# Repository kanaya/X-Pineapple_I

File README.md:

# Pineapple I

Pineapple I is a MIDI-connected 12-way LED driver. Please read doc/pineapple1.md for more info.

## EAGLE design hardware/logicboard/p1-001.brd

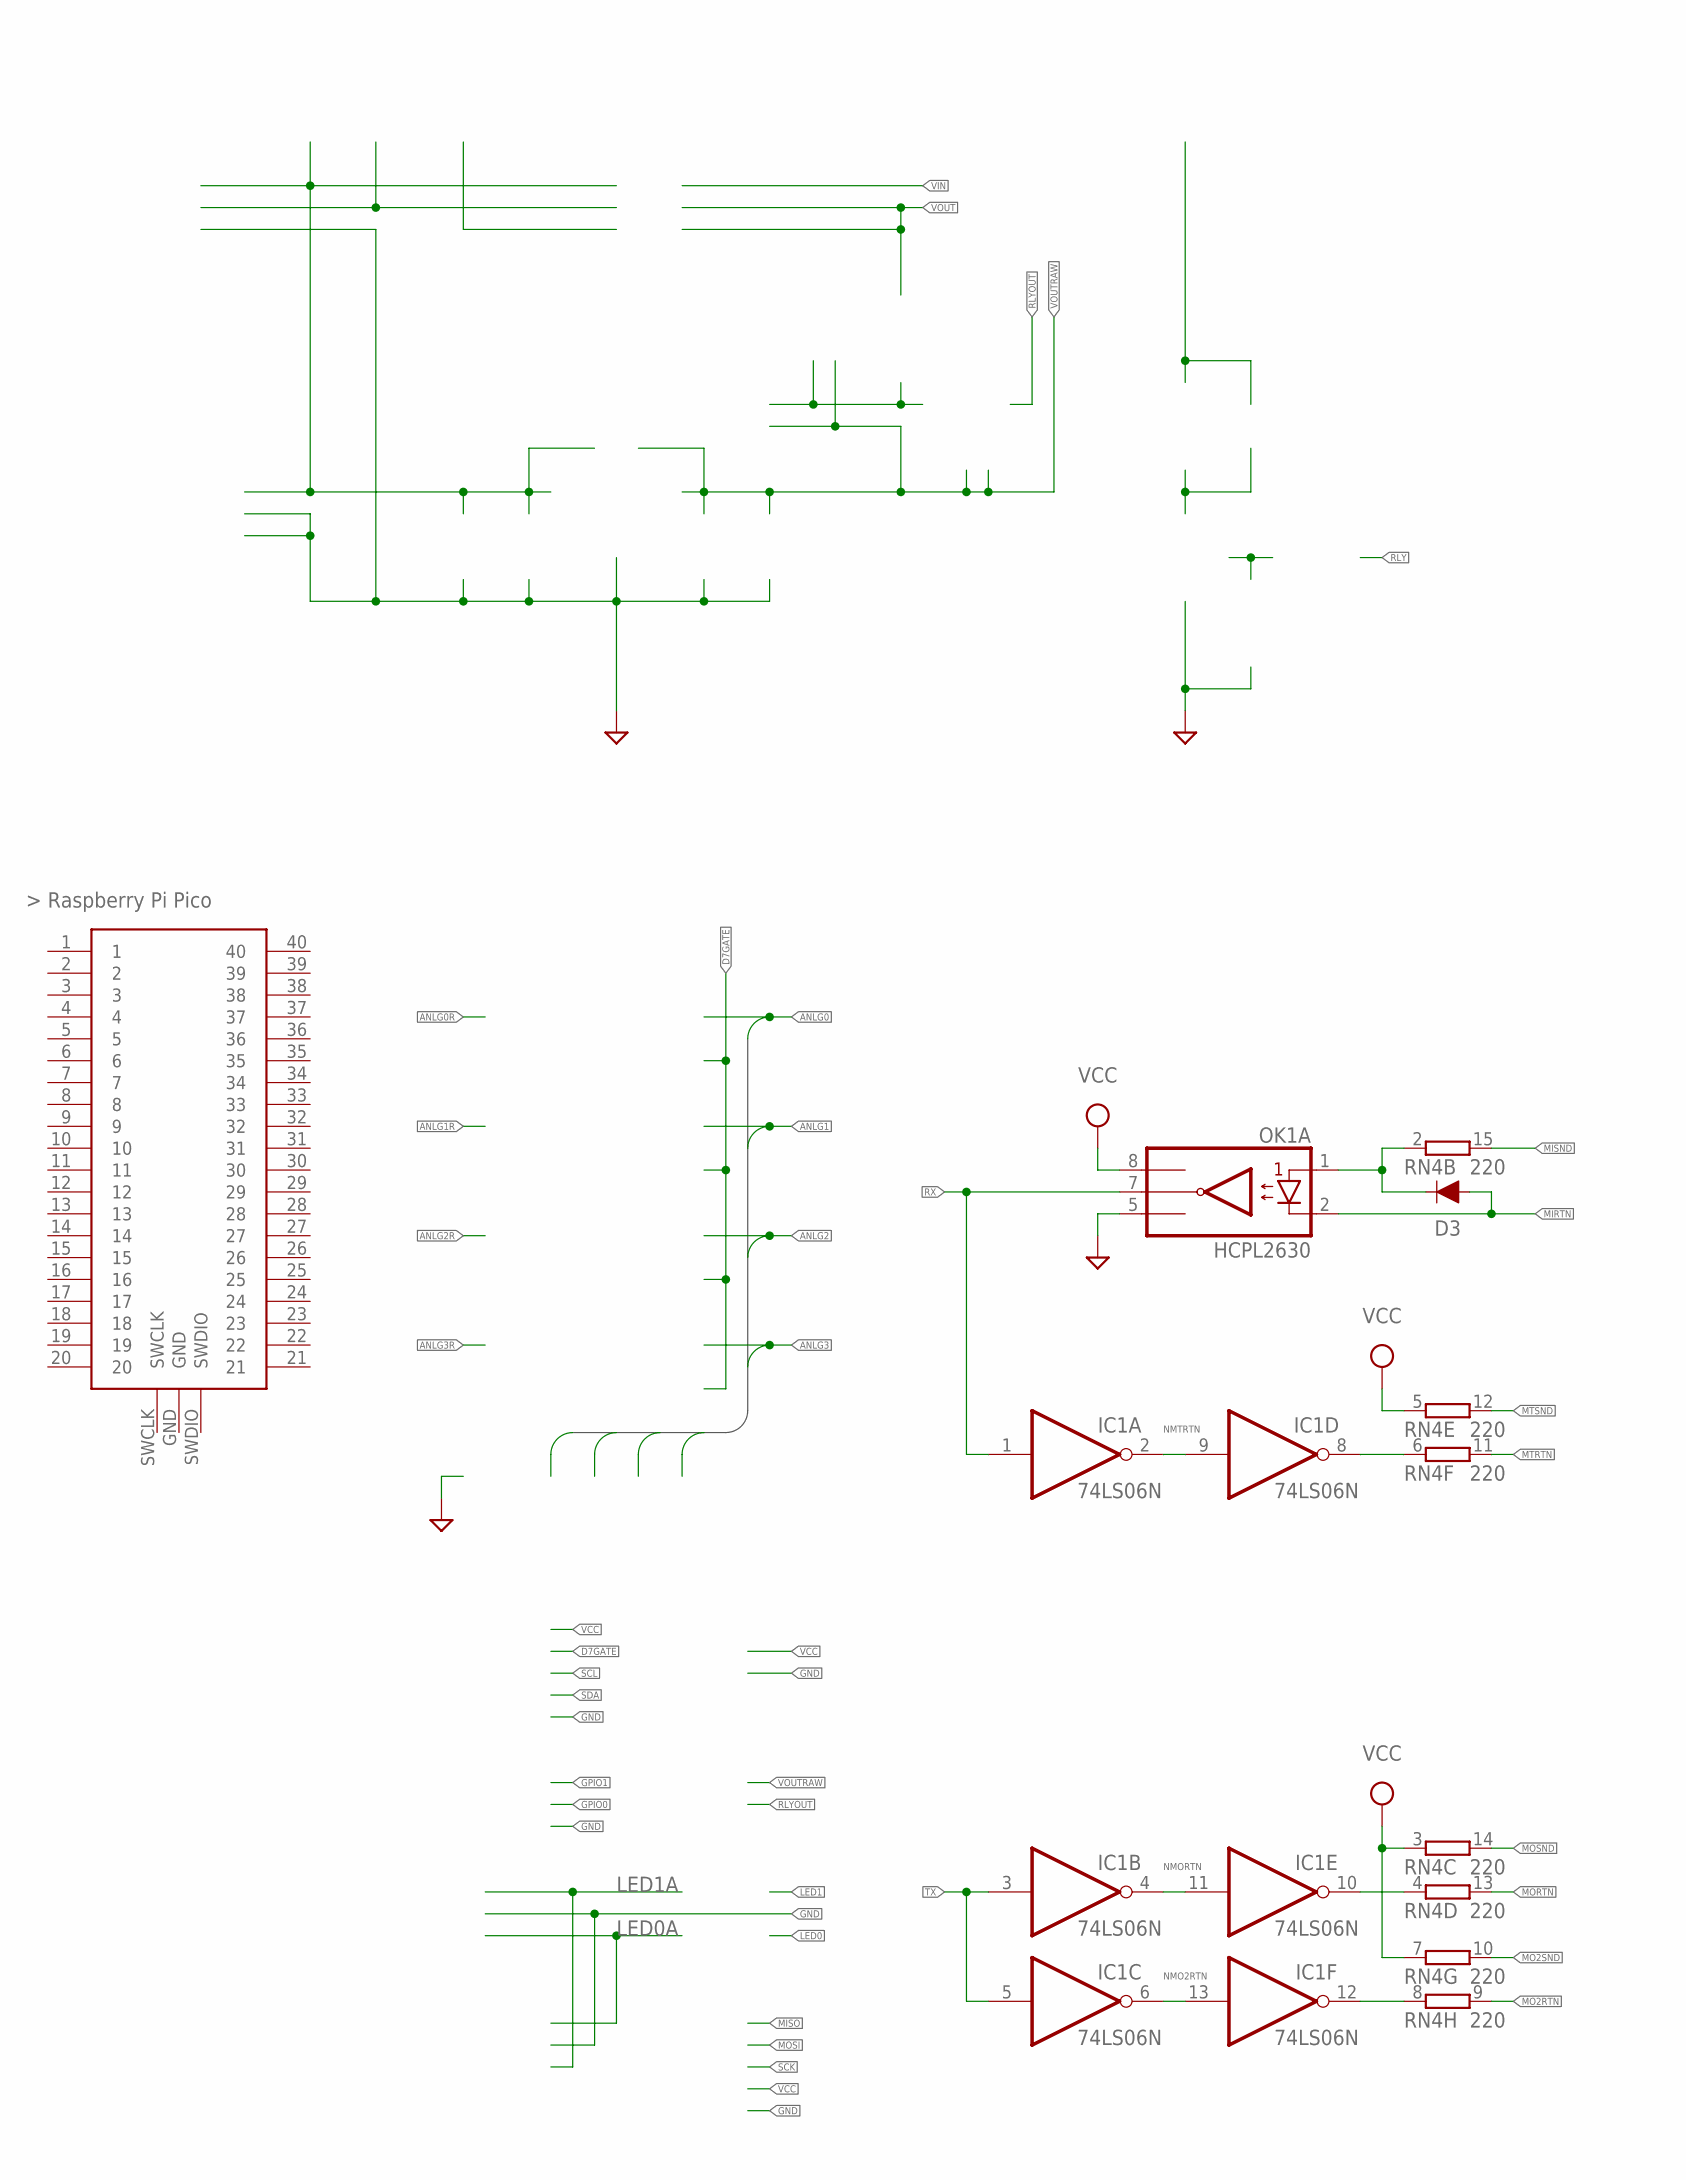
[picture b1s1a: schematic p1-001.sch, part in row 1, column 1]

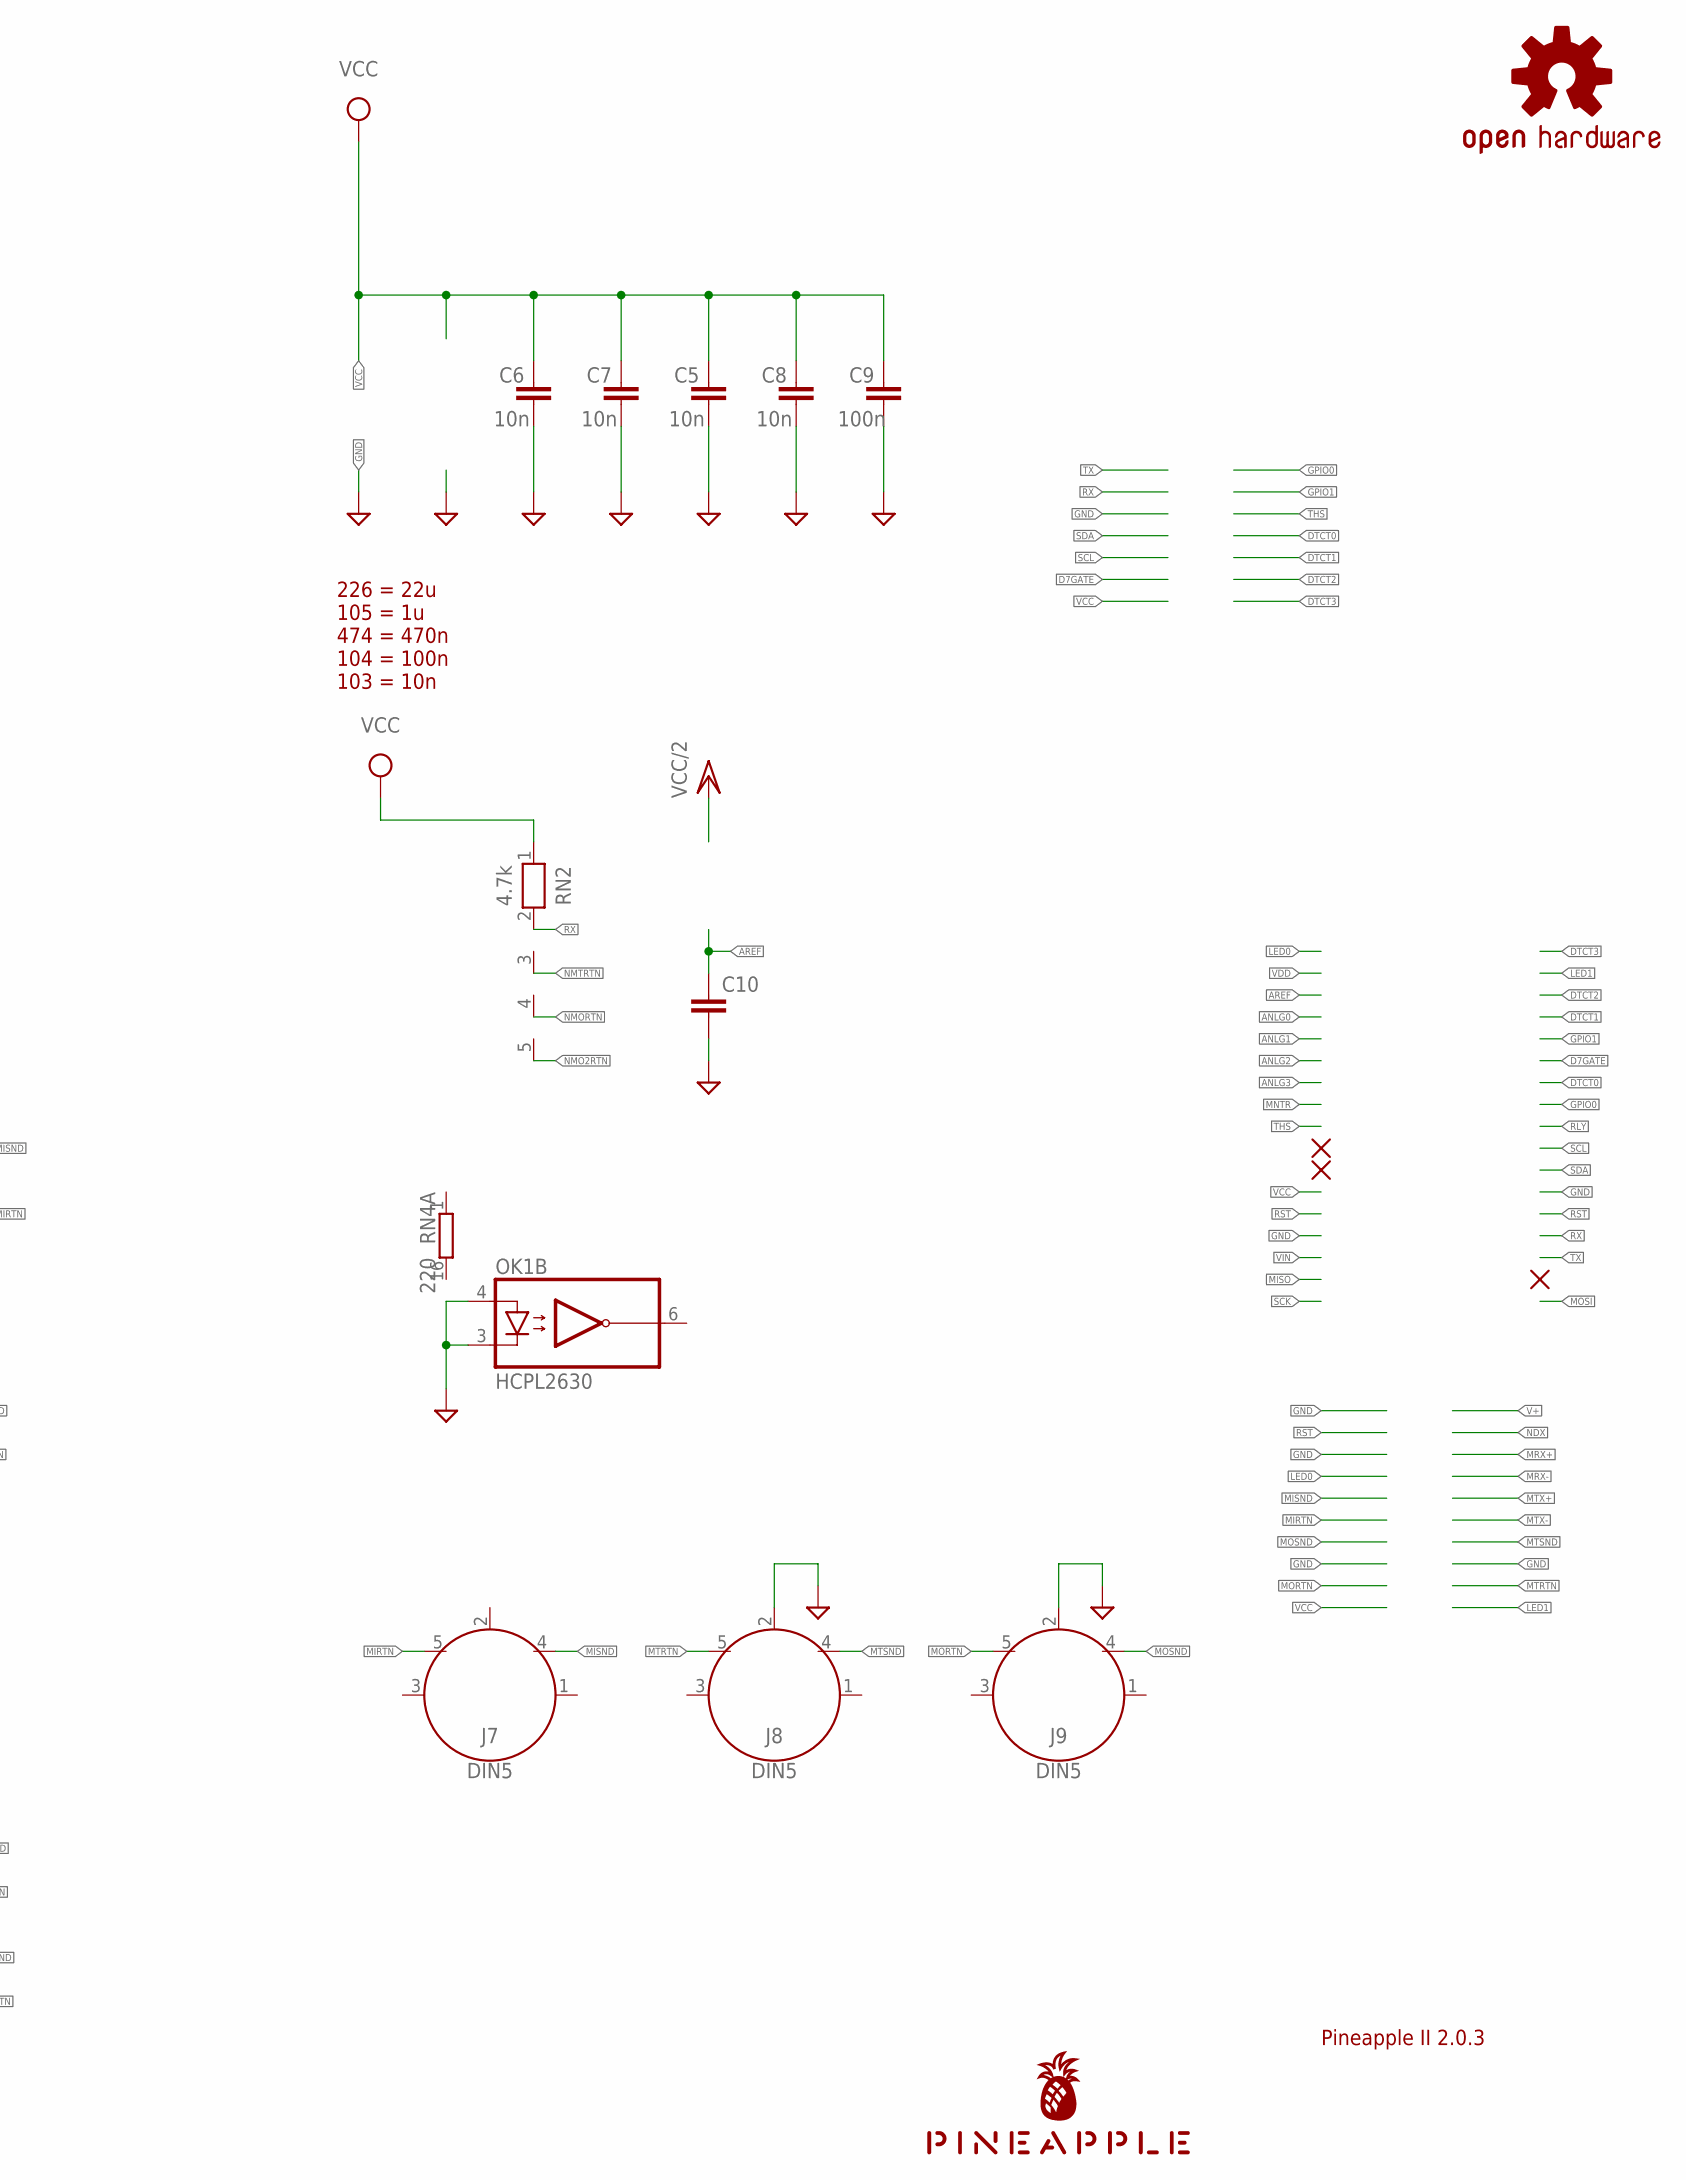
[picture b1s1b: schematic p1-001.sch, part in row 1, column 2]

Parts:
C5, C6, C7, C8: 10n; C025-024X044
C9, C10: 100n; C025-024X044
D3: DIODE-1N4148
IC1: 74LS06N; DIL14
J7, J8, J9: DIN5; DIN5-RA-PTH
LOGO1: OSHW-LOGOS-COPPER; OSHW-LOGO-S_COPPER
OK1: HCPL2630; DIL08
RN2: 4.7k; RN-5
RN4: 220; DIL16
U$1: PINEAPPLE450_SILK
U$2: RASPBERRY-PI-PICO_TH; FT_RASPBERRY-PI-PICO_TH

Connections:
AREF: C10.1
GND: C5.2, C6.2, C7.2, C8.2, C9.2, C10.2, IC1.7 (GND), J8.2, J9.2, OK1.3 (C2), OK1.4 (A2), OK1.5 (GND)
MIDIINSND: D3.C, OK1.1 (A1), RN4.2 (1)
MIRTN: D3.A, J7.5, OK1.2 (C1)
MISND: J7.4, RN4.15 (2)
MO2RTN: RN4.9 (2)
MO2SND: RN4.10 (2)
MORTN: J9.5, RN4.13 (2)
MOSND: J9.4, RN4.14 (2)
MTRTN: J8.5, RN4.11 (2)
MTSND: J8.4, RN4.12 (2)
unnamed: IC1.8 (O), RN4.6 (1)
unnamed: IC1.10 (O), RN4.4 (1)
unnamed: IC1.12 (O), RN4.8 (1)
NMO2RTN: IC1.6 (O), IC1.13 (I), RN2.5
NMORTN: IC1.4 (O), IC1.11 (I), RN2.4
NMTRTN: IC1.2 (O), IC1.9 (I), RN2.3
RX: IC1.1 (I), OK1.7 (VO1), RN2.2
TX: IC1.3 (I), IC1.5 (I)
VCC: C5.1, C6.1, C7.1, C8.1, C9.1, IC1.14 (VCC), OK1.8 (VCC), RN2.1, RN4.3 (1), RN4.5 (1), RN4.7 (1)

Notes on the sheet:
Pineapple II 2.0.3
226 = 22u 105 = 1u 474 = 470n 104 = 100n 103 = 10n

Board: 2 copper layers, 17 parts (0 on the bottom side), 17 nets, no tracks yet.

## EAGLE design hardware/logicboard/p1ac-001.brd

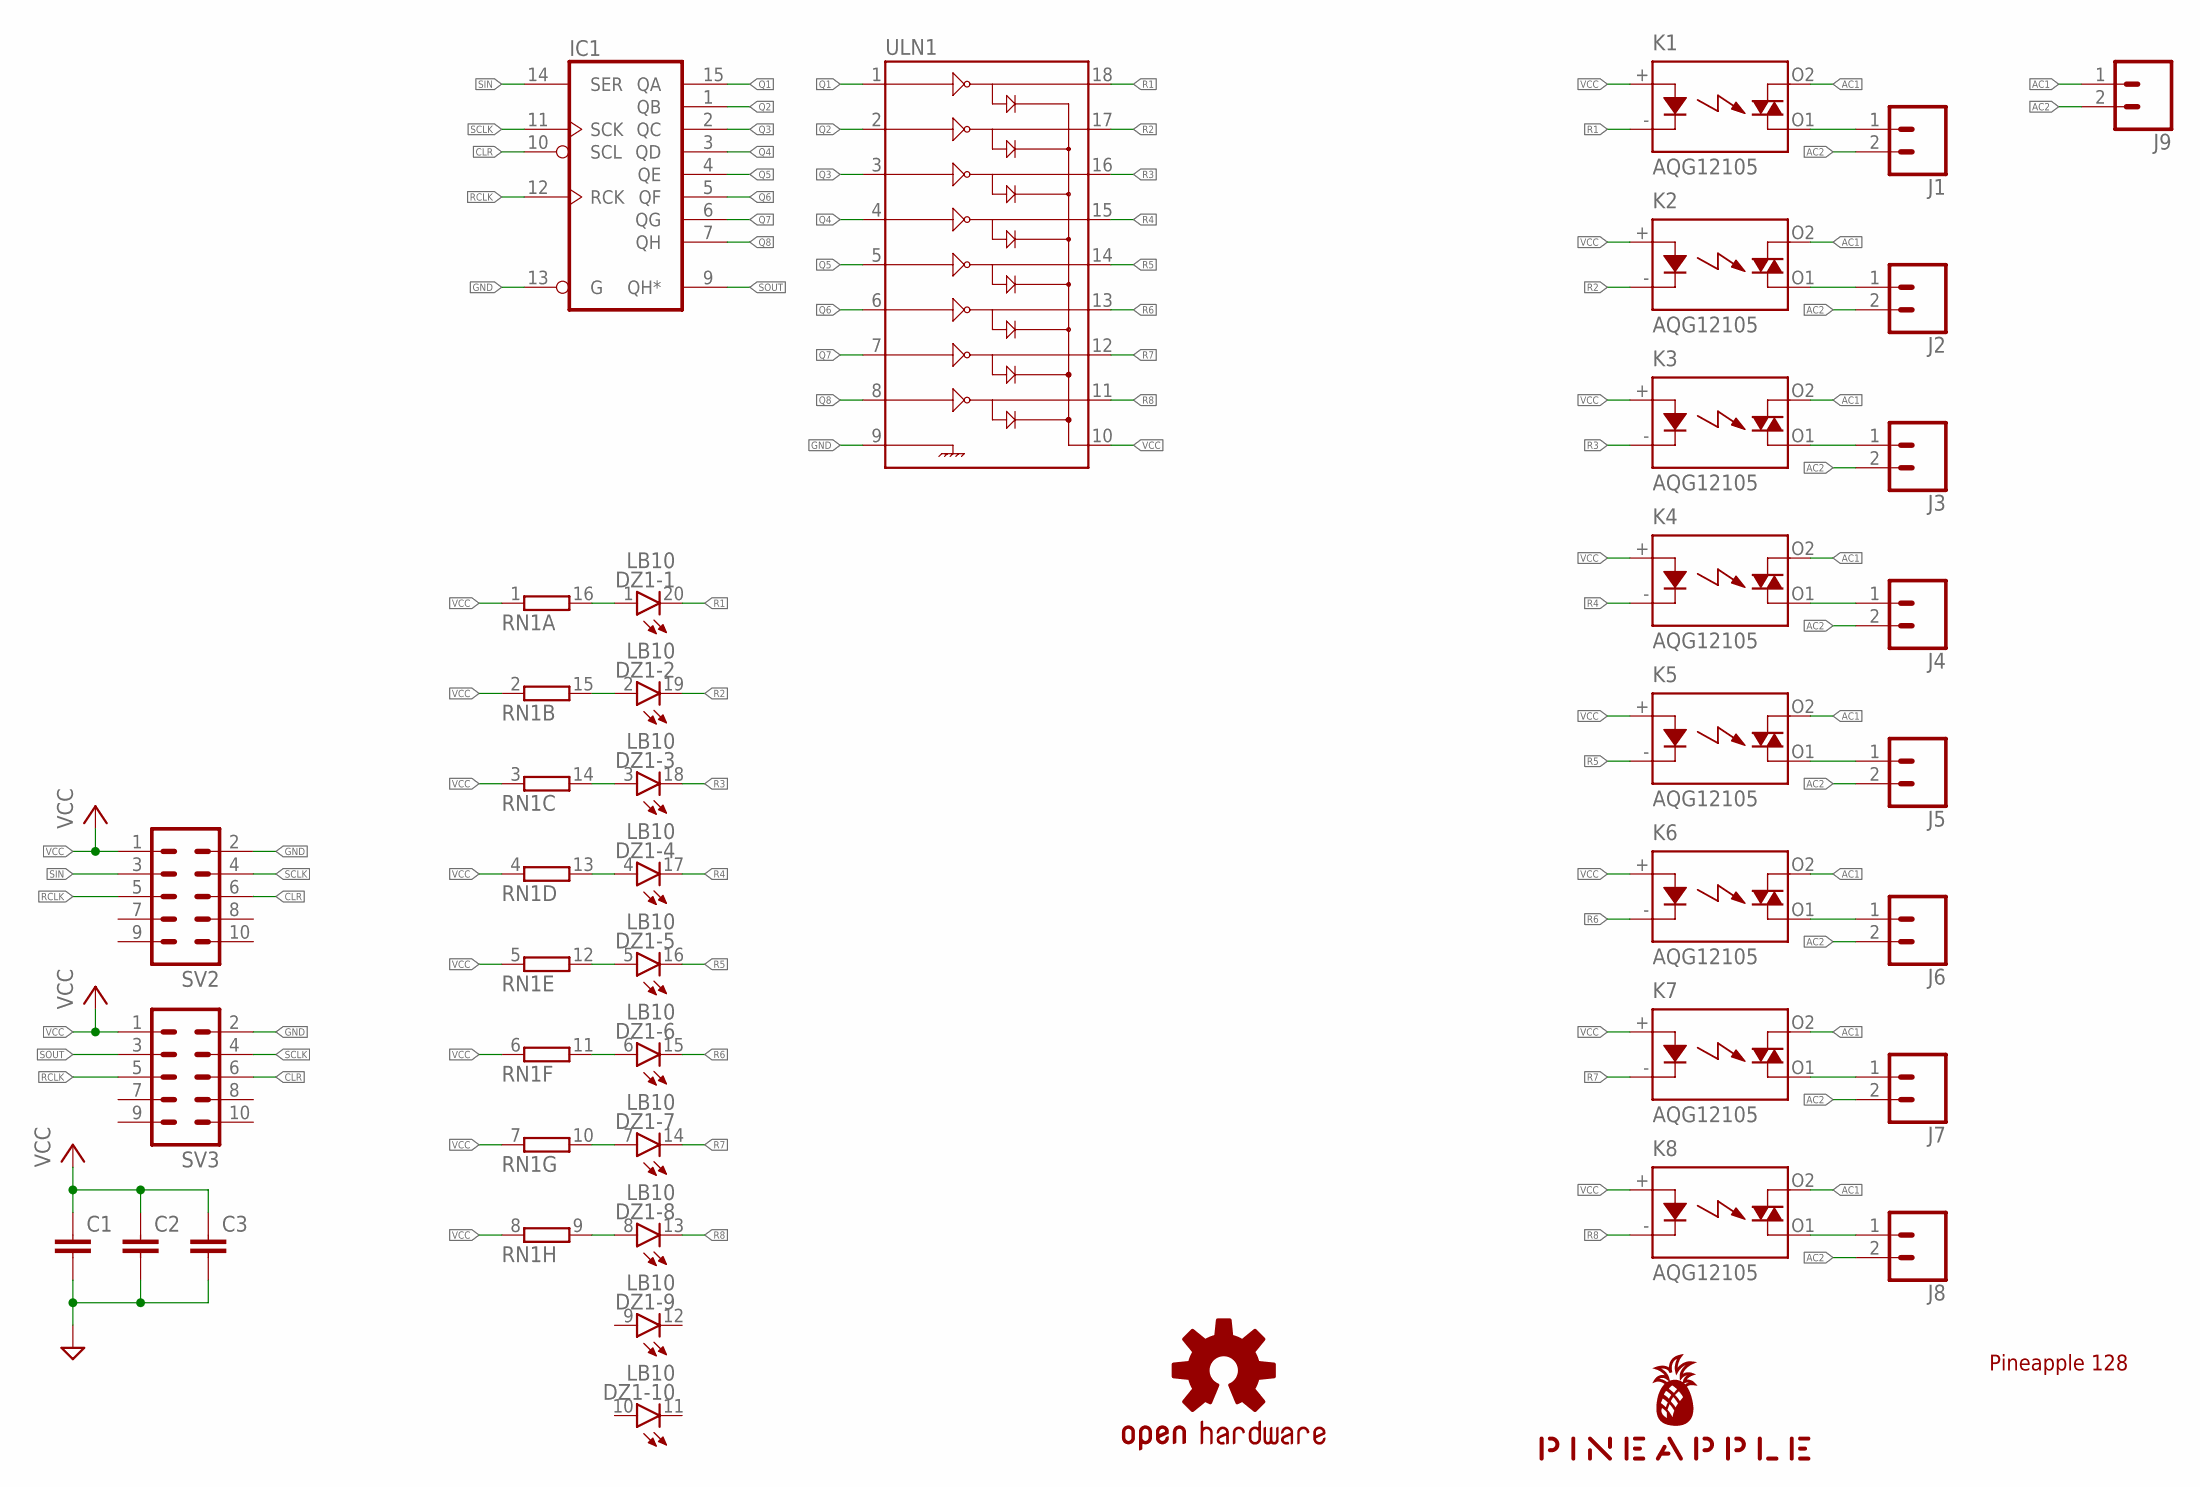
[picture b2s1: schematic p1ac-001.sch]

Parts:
C1, C2, C3: C-EU025-024X044; C025-024X044
DZ1: LB10
IC1: 74LS595N; DIL16
J1, J2, J3, J4, J5, J6, J7, J8, J9: CONN_02POLAR; MOLEX-1X2
K1, K2, K3, K4, K5, K6, K7, K8: AQG12105; AQG
LOGO1: OSHW-LOGOS-COPPER; OSHW-LOGO-S_COPPER
RN1: 8R-N; DIL16
SV2, SV3: ML10L
U$1: PINEAPPLE450_SILK
ULN1: ULN2803DIP; DIL18

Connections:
AC1: J9.1, K1.O2 (DS1), K2.O2 (DS1), K3.O2 (DS1), K4.O2 (DS1), K5.O2 (DS1), K6.O2 (DS1), K7.O2 (DS1), K8.O2 (DS1)
AC2: J1.2, J2.2, J3.2, J4.2, J5.2, J6.2, J7.2, J8.2, J9.2
CLR: IC1.10 (SCL), SV2.6, SV3.6
GND: C1.2, C2.2, C3.2, IC1.8 (GND), IC1.13 (G), SV2.2, SV3.2, ULN1.9
unnamed: DZ1.1 (A), RN1.16 (2)
unnamed: DZ1.2 (A), RN1.15 (2)
unnamed: DZ1.3 (A), RN1.14 (2)
unnamed: DZ1.4 (A), RN1.13 (2)
unnamed: DZ1.5 (A), RN1.12 (2)
unnamed: DZ1.6 (A), RN1.11 (2)
unnamed: DZ1.7 (A), RN1.10 (2)
unnamed: DZ1.8 (A), RN1.9 (2)
Q1: IC1.15 (QA), ULN1.1
Q2: IC1.1 (QB), ULN1.2
Q3: IC1.2 (QC), ULN1.3
Q4: IC1.3 (QD), ULN1.4
Q5: IC1.4 (QE), ULN1.5
Q6: IC1.5 (QF), ULN1.6
Q7: IC1.6 (QG), ULN1.7
Q8: IC1.7 (QH), ULN1.8
R1: DZ1.20 (C), K1.- (K), ULN1.18
R2: DZ1.19 (C), K2.- (K), ULN1.17
R3: DZ1.18 (C), K3.- (K), ULN1.16
R4: DZ1.17 (C), K4.- (K), ULN1.15
R5: DZ1.16 (C), K5.- (K), ULN1.14
R6: DZ1.15 (C), K6.- (K), ULN1.13
R7: DZ1.14 (C), K7.- (K), ULN1.12
R8: DZ1.13 (C), K8.- (K), ULN1.11
RCLK: IC1.12 (RCK), SV2.5, SV3.5
SCLK: IC1.11 (SCK), SV2.4, SV3.4
SIN: IC1.14 (SER), SV2.3
SOUT: IC1.9 (QH*), SV3.3
VCC: C1.1, C2.1, C3.1, IC1.16 (VCC), K1.+ (A), K2.+ (A), K3.+ (A), K4.+ (A), K5.+ (A), K6.+ (A), K7.+ (A), K8.+ (A), RN1.1, RN1.2 (1), RN1.3 (1), RN1.4 (1), RN1.5 (1), RN1.6 (1), RN1.7 (1), RN1.8 (1), SV2.1, SV3.1, ULN1.10
X1: J1.1, K1.O1 (DS2)
X2: J2.1, K2.O1 (DS2)
X3: J3.1, K3.O1 (DS2)
X4: J4.1, K4.O1 (DS2)
X5: J5.1, K5.O1 (DS2)
X6: J6.1, K6.O1 (DS2)
X7: J7.1, K7.O1 (DS2)
X8: J8.1, K8.O1 (DS2)

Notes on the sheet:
Pineapple 128

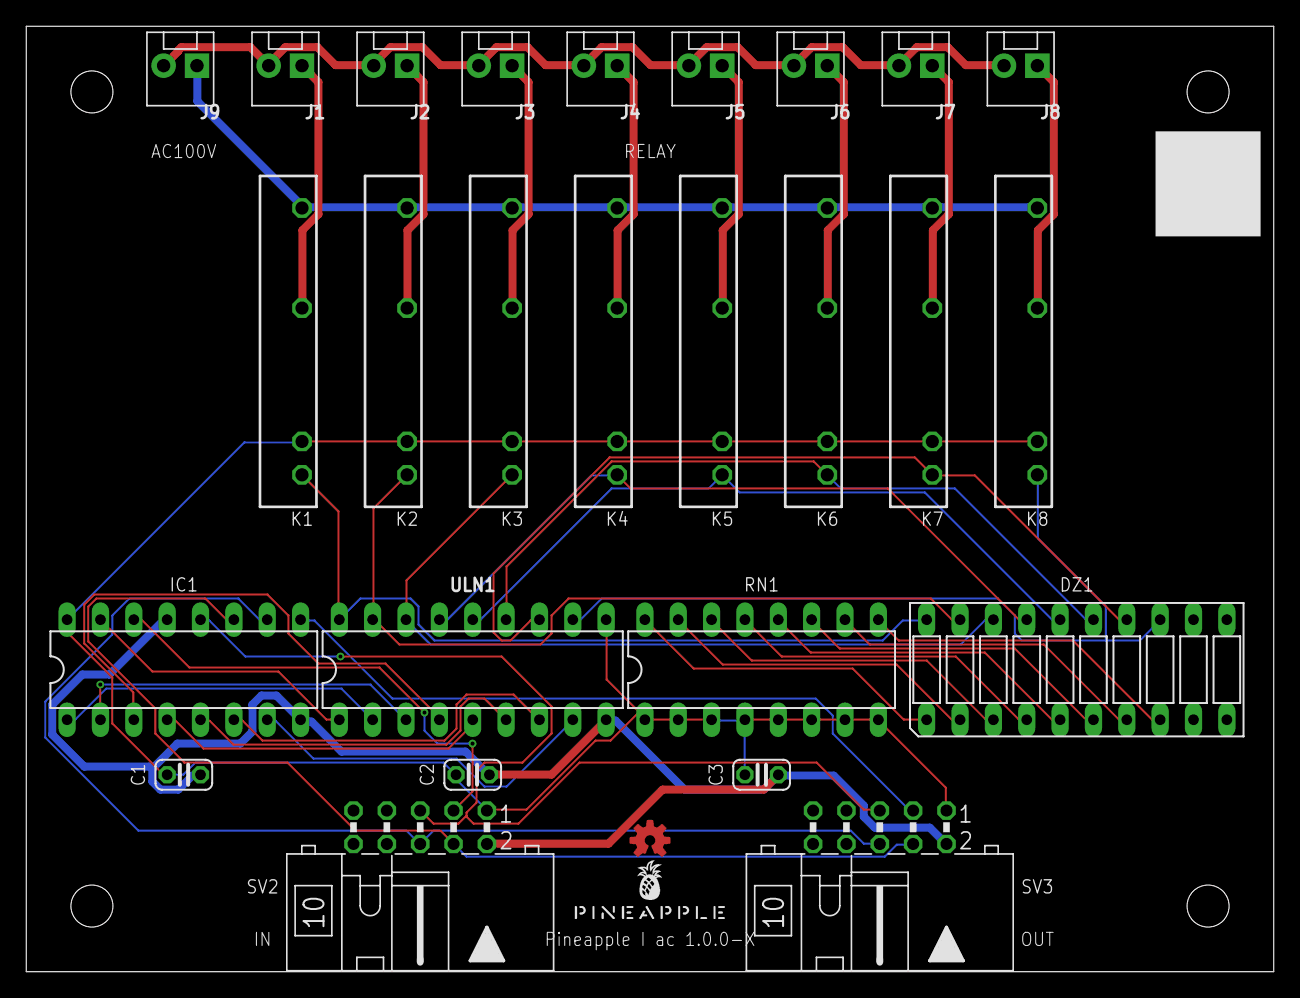
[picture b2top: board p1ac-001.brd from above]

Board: 2 copper layers, 95.0 x 72.0 mm, 28 parts (0 on the bottom side), 41 nets.

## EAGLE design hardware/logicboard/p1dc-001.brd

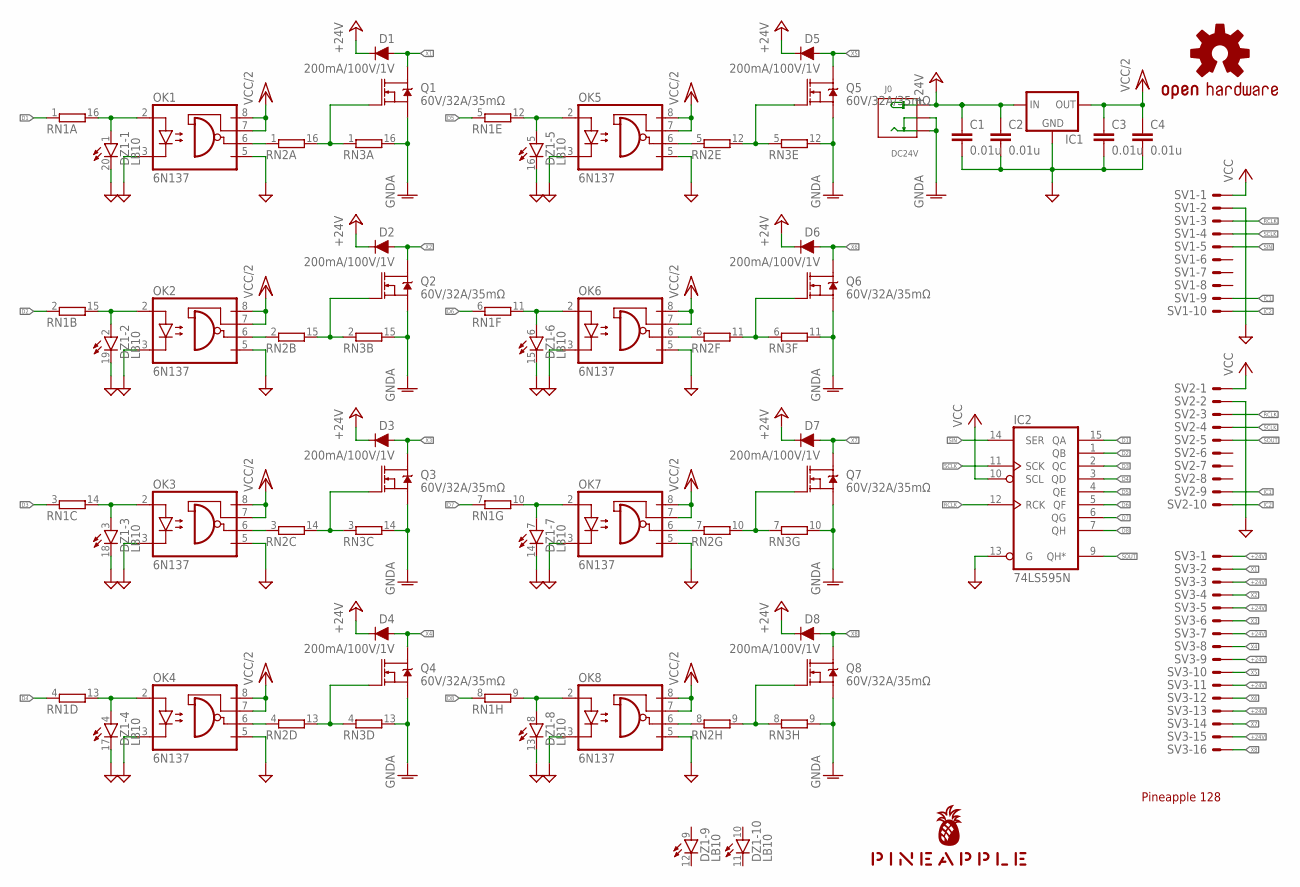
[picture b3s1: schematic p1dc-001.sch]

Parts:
C1, C2, C3, C4: 0.01u; C025-024X044
D1, D2, D3, D4, D5, D6, D7, D8: 200mA/100V/1V; DIODE-1N4148
DZ1: LB10
IC1: 78XXS
IC2: 74LS595N; DIL16
J0: DC24V; 3P-L14.2*W11.0*H9.0MM
LOGO1: OSHW-LOGOS-COPPER; OSHW-LOGO-S_COPPER
OK1, OK2, OK3, OK4, OK5, OK6, OK7, OK8: 6N137; DIL08
Q1, Q2, Q3, Q4, Q5, Q6, Q7, Q8: 60V/32A/35mΩ; TO220V
RN1, RN2, RN3: 8R-N; DIL16
SV1, SV2: ML10LE; ML10L
SV3: ML16LE; ML16L
U$1: PINEAPPLE450_SILK

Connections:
+24V: C1.1, C2.1, D1.C, D2.C, D3.C, D4.C, D5.C, D6.C, D7.C, D8.C, IC1.IN, J0.+, SV3.1, SV3.3, SV3.5, SV3.7, SV3.9, SV3.11, SV3.13, SV3.15
GND: C1.2, C2.2, C3.2, C4.2, DZ1.13 (C), DZ1.14 (C), DZ1.15 (C), DZ1.16 (C), DZ1.17 (C), DZ1.18 (C), DZ1.19 (C), DZ1.20 (C), IC1.GND, IC2.8 (GND), IC2.13 (G), OK1.3 (C), OK1.5 (GND), OK2.3 (C), OK2.5 (GND), OK3.3 (C), OK3.5 (GND), OK4.3 (C), OK4.5 (GND), OK5.3 (C), OK5.5 (GND), OK6.3 (C), OK6.5 (GND), OK7.3 (C), OK7.5 (GND), OK8.3 (C), OK8.5 (GND), SV1.2, SV2.2
GNDA: J0.-1 (-), J0.-2 (CDN), Q1.3 (S), Q2.3 (S), Q3.3 (S), Q4.3 (S), Q5.3 (S), Q6.3 (S), Q7.3 (S), Q8.3 (S), RN3.9 (2), RN3.10 (2), RN3.11 (2), RN3.12 (2), RN3.13 (2), RN3.14 (2), RN3.15 (2), RN3.16 (2)
IC1: SV1.9, SV2.9
IC2: SV1.10, SV2.10
unnamed: DZ1.1 (A), OK1.2 (A), RN1.16 (2)
unnamed: OK1.6 (VO), RN2.1
unnamed: Q1.1 (G), RN2.16 (2), RN3.1
unnamed: DZ1.2 (A), OK2.2 (A), RN1.15 (2)
unnamed: OK2.6 (VO), RN2.2 (1)
unnamed: Q2.1 (G), RN2.15 (2), RN3.2 (1)
unnamed: DZ1.3 (A), OK3.2 (A), RN1.14 (2)
unnamed: OK3.6 (VO), RN2.3 (1)
unnamed: Q3.1 (G), RN2.14 (2), RN3.3 (1)
unnamed: DZ1.4 (A), OK4.2 (A), RN1.13 (2)
unnamed: OK4.6 (VO), RN2.4 (1)
unnamed: Q4.1 (G), RN2.13 (2), RN3.4 (1)
unnamed: DZ1.5 (A), OK5.2 (A), RN1.12 (2)
unnamed: OK5.6 (VO), RN2.5 (1)
unnamed: Q5.1 (G), RN2.12 (2), RN3.5 (1)
unnamed: DZ1.6 (A), OK6.2 (A), RN1.11 (2)
unnamed: OK6.6 (VO), RN2.6 (1)
unnamed: Q6.1 (G), RN2.11 (2), RN3.6 (1)
unnamed: DZ1.7 (A), OK7.2 (A), RN1.10 (2)
unnamed: OK7.6 (VO), RN2.7 (1)
unnamed: Q7.1 (G), RN2.10 (2), RN3.7 (1)
unnamed: DZ1.8 (A), OK8.2 (A), RN1.9 (2)
unnamed: OK8.6 (VO), RN2.8 (1)
unnamed: Q8.1 (G), RN2.9 (2), RN3.8 (1)
Q1: IC2.15 (QA), RN1.1
Q2: IC2.1 (QB), RN1.2 (1)
Q3: IC2.2 (QC), RN1.3 (1)
Q4: IC2.3 (QD), RN1.4 (1)
Q6: IC2.5 (QF), RN1.6 (1)
Q7: IC2.6 (QG), RN1.7 (1)
Q8: IC2.7 (QH), RN1.8 (1)
RCLK: IC2.12 (RCK), SV1.3, SV2.3
SCLK: IC2.11 (SCK), SV1.4, SV2.4
SIN: IC2.14 (SER), SV1.5
SOUT: IC2.9 (QH*), SV2.5
VCC: IC2.10 (SCL), IC2.16 (VCC), SV1.1, SV2.1
VCC/2: C3.1, C4.1, IC1.OUT, OK1.7 (VE), OK1.8 (VCC), OK2.7 (VE), OK2.8 (VCC), OK3.7 (VE), OK3.8 (VCC), OK4.7 (VE), OK4.8 (VCC), OK5.7 (VE), OK5.8 (VCC), OK6.7 (VE), OK6.8 (VCC), OK7.7 (VE), OK7.8 (VCC), OK8.7 (VE), OK8.8 (VCC)
X1: D1.A, Q1.2 (D), SV3.2
X2: D2.A, Q2.2 (D), SV3.4
X3: D3.A, Q3.2 (D), SV3.6
X4: D4.A, Q4.2 (D), SV3.8
X5: D5.A, Q5.2 (D), SV3.10
X6: D6.A, Q6.2 (D), SV3.12
X7: D7.A, Q7.2 (D), SV3.14
X8: D8.A, Q8.2 (D), SV3.16

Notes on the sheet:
Pineapple 128

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
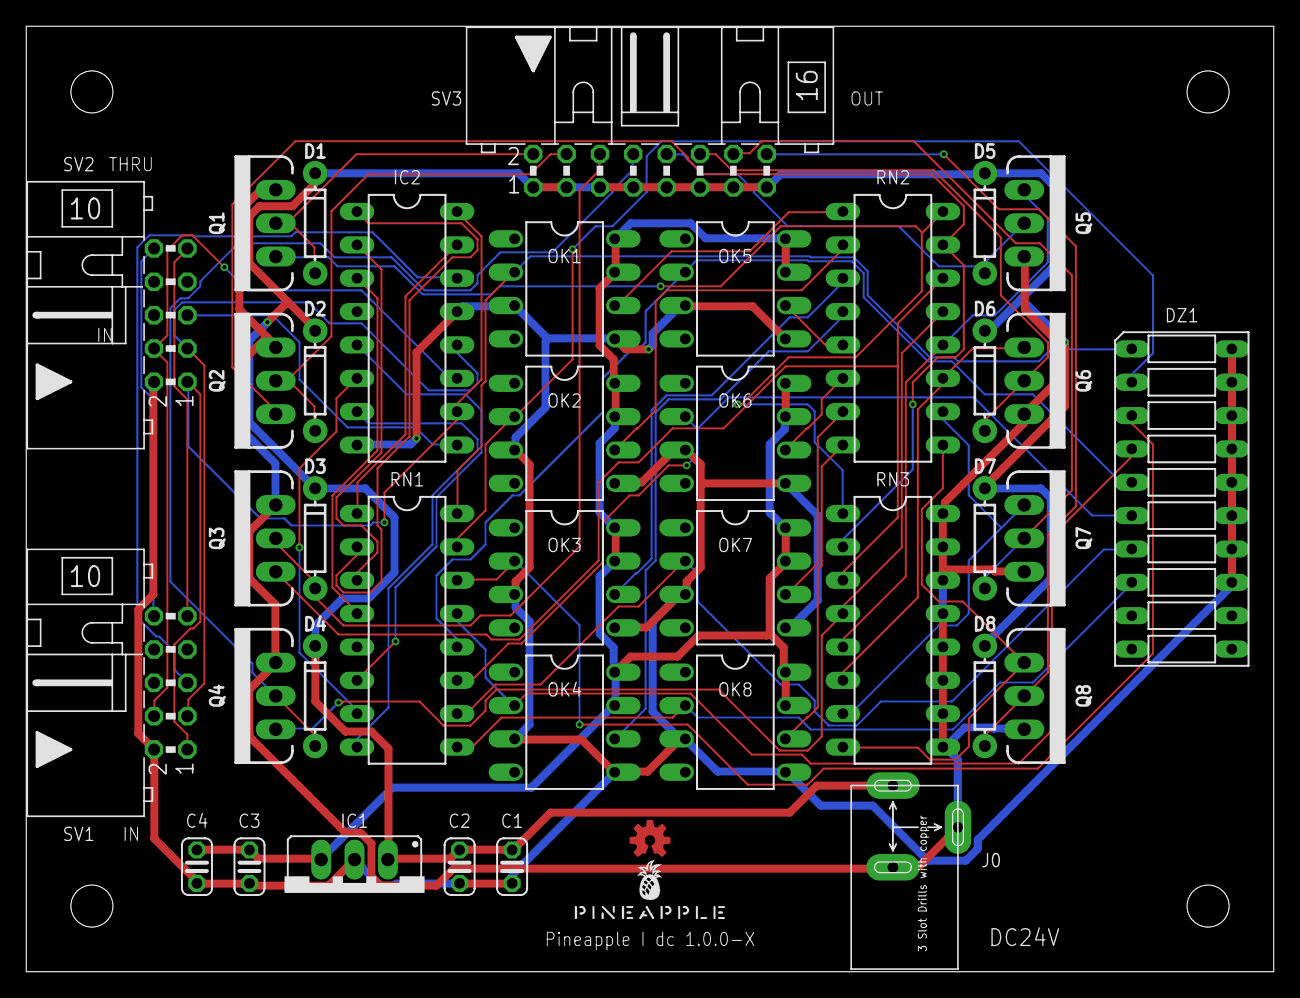
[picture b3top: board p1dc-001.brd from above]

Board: 2 copper layers, 94.9 x 71.9 mm, 40 parts (0 on the bottom side), 50 nets.

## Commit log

2018-03-06 Initinal doc.
2018-03-06 Added MPU pinout.
2018-03-06 Doc update.
2018-03-10 Almost initial commit.
2018-03-10 Moved silk pattern of front panel.
2018-03-10 Renew.
2018-03-10 Changed internal bus name.
2018-03-11 Added (forgotten) LED port.
2018-03-11 P-ban data.
2018-03-11 AltDrive port.
2018-03-11 Refine schematic.
2018-03-11 Fixed (missed) LED resistors.
2018-03-12 Moved AltDrive position and added new drill holes.
2018-03-16 Silk update.
2018-03-16 Update silk.
2018-03-16 Fixed missing silk pattern.
2018-03-16 Fixed doc.
2018-03-16 Swapped pin D7 and D12.
2018-03-17 1-Wire ROM.
2018-03-17 Document update.
2018-03-18 Changed silk pattern.
2018-03-18 Relay.
2018-03-19 Fixed small errors.
2018-03-19 Readability update.
2018-03-19 Reroute.
2018-03-19 Pull-up resistors for I2C.
2018-07-14 New pinout.
2018-07-16 New design.
2018-07-16 New layout.
2018-07-16 Small factor.
2018-07-18 Refine.
2018-07-19 Removed panel1.
2018-07-19 Silk.
2018-07-19 Added MKR compatible I2C connector.
2018-07-19 Layout.
2018-07-19 New silk.
2018-07-20 20 holes.
2018-07-24 Vcc and Vref terminal.
2018-07-24 I2C pull-up.
2018-07-25 Doc.
2018-07-25 New analog/reserve ports.
2018-07-25 Reserve pins.
2018-07-26 Renumbered.
2018-07-26 Component list.
2018-07-29 New reset signal pattern.
2018-08-03 .gitignore.
2018-08-03 Clean up.
2018-08-04 1mm exterior.
2018-08-05 Fixing exterior.
2018-08-06 Fixed soldering mask.
2018-08-09 Added restricted zone.
2018-08-11 OSHW logo.
2018-08-13 Pineapple logo v2.
2018-08-13 New pineapple logo.
2018-08-14 Changed signal names.
2018-08-14 Added Makefile.
2018-08-15 Version 1.0.1 -> 1.2.0.
2018-08-21 Pineapple Logo (vector->bitmap), OSHW logo (silk -> copper).
2018-08-22 Changed font size of the silk pattern.
2018-09-05 Unified MIDI connector.
2018-09-16 Fixed positions of front connectors.
2018-09-16 Added screenshot of the schematic (release/1.2.0).
2020-06-25 FET board.
2020-06-25 Imported new design of Pineapple I from "catbit" project.
2020-06-25 Added MIDI IN.
2020-06-26 Renamed P1s to P1dc.
2020-06-26 Imported old version of Pineapple 128 as Pineapple I ac.
2020-06-26 First shot.
2020-06-26 Board design.
2020-06-26 Working.
2020-06-26 Clean up of the board design of Pineapple I dc driver.
2020-06-26 Board design of Pineapple I ac driver.
2022-02-09 Imported from Pineapple IIb 2.5.2-RC.
2022-02-09 Added Pico and removed unnecessary components.
2022-02-09 Removed many things.

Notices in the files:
parts and their libraries:
SparkFun-DiscreteSemi: Licensing: Creative Commons ShareAlike 4.0 International - https://creativecommons.org/licenses/by-sa/4.0
